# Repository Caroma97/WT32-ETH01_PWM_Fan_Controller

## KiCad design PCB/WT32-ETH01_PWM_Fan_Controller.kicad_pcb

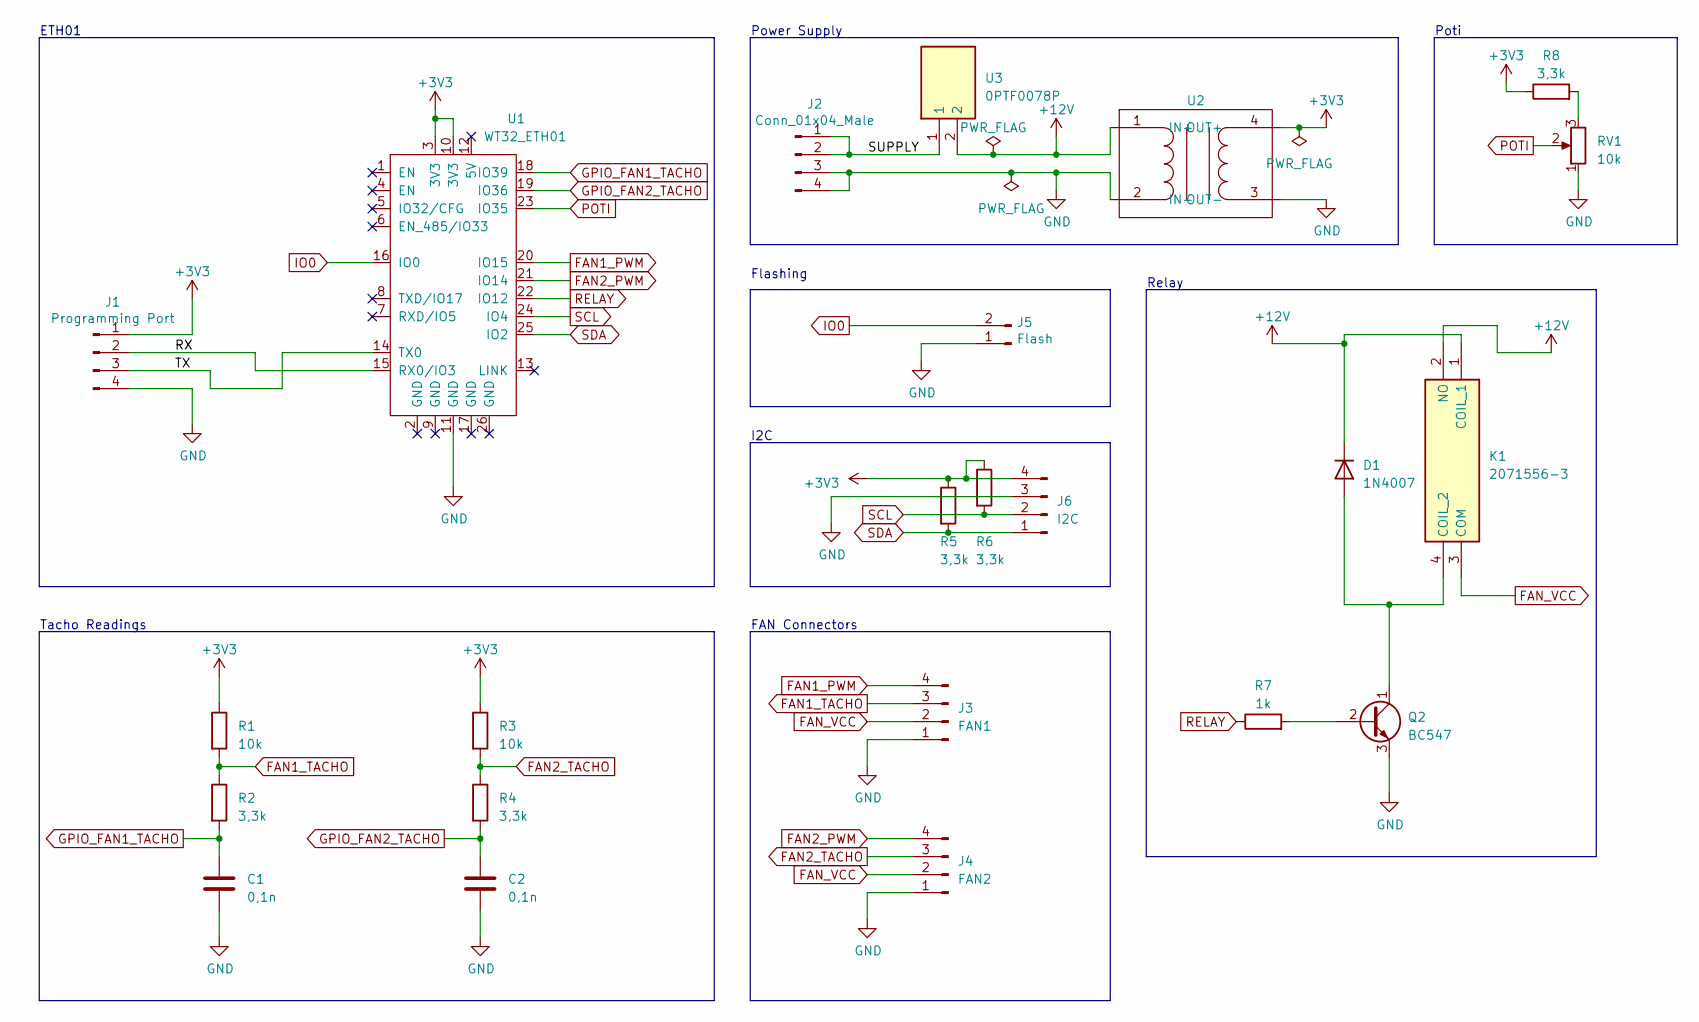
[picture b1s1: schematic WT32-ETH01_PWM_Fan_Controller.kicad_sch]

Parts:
C1, C2: 0,1n; C_Rect_L4.6mm_W2.0mm_P2.50mm_MKS02_FKP02
D1: 1N4007; D_DO-41_SOD81_P10.16mm_Horizontal
J1: Programming Port; PinHeader_1x04_P2.54mm_Vertical
J2: Conn_01x04_Male; TerminalBlock_Phoenix_MPT-0,5-4-2.54_1x04_P2.54mm_Horizontal
J3: FAN1; FanPinHeader_1x04_P2.54mm_Vertical
J4: FAN2; FanPinHeader_1x04_P2.54mm_Vertical
J5: Flash; PinHeader_1x02_P2.54mm_Vertical
J6: I2C; PinHeader_1x04_P2.54mm_Vertical
K1: 2071556-3; 20715563; Mouser Part Number 655-2071556-3
Q2: BC547; TO-92_Inline
R1, R3: 10k; R_1206_3216Metric_Pad1.30x1.75mm_HandSolder
R2, R4, R5, R6, R8: 3,3k; R_1206_3216Metric_Pad1.30x1.75mm_HandSolder
R7: 1k; R_1206_3216Metric_Pad1.30x1.75mm_HandSolder
RV1: 10k; PinHeader_1x03_P2.54mm_Vertical
U1: WT32_ETH01
U2: 2596S-ADJ_3A_DC-DC_Step_Down_Buck_Power_Module
U3: 0PTF0078P; Mouser Part Number 576-0PTF0078P

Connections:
+3V3: J1.1, J6.4, R1.1, R3.1, R5.1, R6.1, R8.1, U1.3 (3V3), U1.10 (3V3), U2.4 (OUT+)
+12V: D1.1 (K), K1.1 (COIL_1), K1.2 (NO), U2.1 (IN+), U3.2
/RX: J1.2, U1.15 (RX0/IO3)
/SUPPLY: J2.1, J2.2, U3.1
/TX: J1.3, U1.14 (TX0)
FAN1_PWM: J3.4, U1.20 (IO15)
FAN1_TACHO: J3.3, R1.2, R2.1
FAN2_PWM: J4.4, U1.21 (IO14)
FAN2_TACHO: J4.3, R3.2, R4.1
FAN_VCC: J3.2, J4.2, K1.3 (COM)
GND: C1.2, C2.2, J1.4, J2.3, J2.4, J3.1, J4.1, J5.1, J6.3, Q2.3 (E), RV1.1, U1.11 (GND), U2.2 (IN-), U2.3 (OUT-)
GPIO_FAN1_TACHO: C1.1, R2.2, U1.18 (IO39)
GPIO_FAN2_TACHO: C2.1, R4.2, U1.19 (IO36)
IO0: J5.2, U1.16 (IO0)
unnamed: D1.2 (A), K1.4 (COIL_2), Q2.1 (C)
unnamed: Q2.2 (B), R7.2
unnamed: R8.2, RV1.3
POTI: RV1.2, U1.23 (IO35)
RELAY: R7.1, U1.22 (IO12)
SCL: J6.2, R6.2, U1.24 (IO4)
SDA: J6.1, R5.2, U1.25 (IO2)

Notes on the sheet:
I2C
Power Supply
ETH01
Tacho Readings
Flashing
FAN Connectors
Poti
Relay

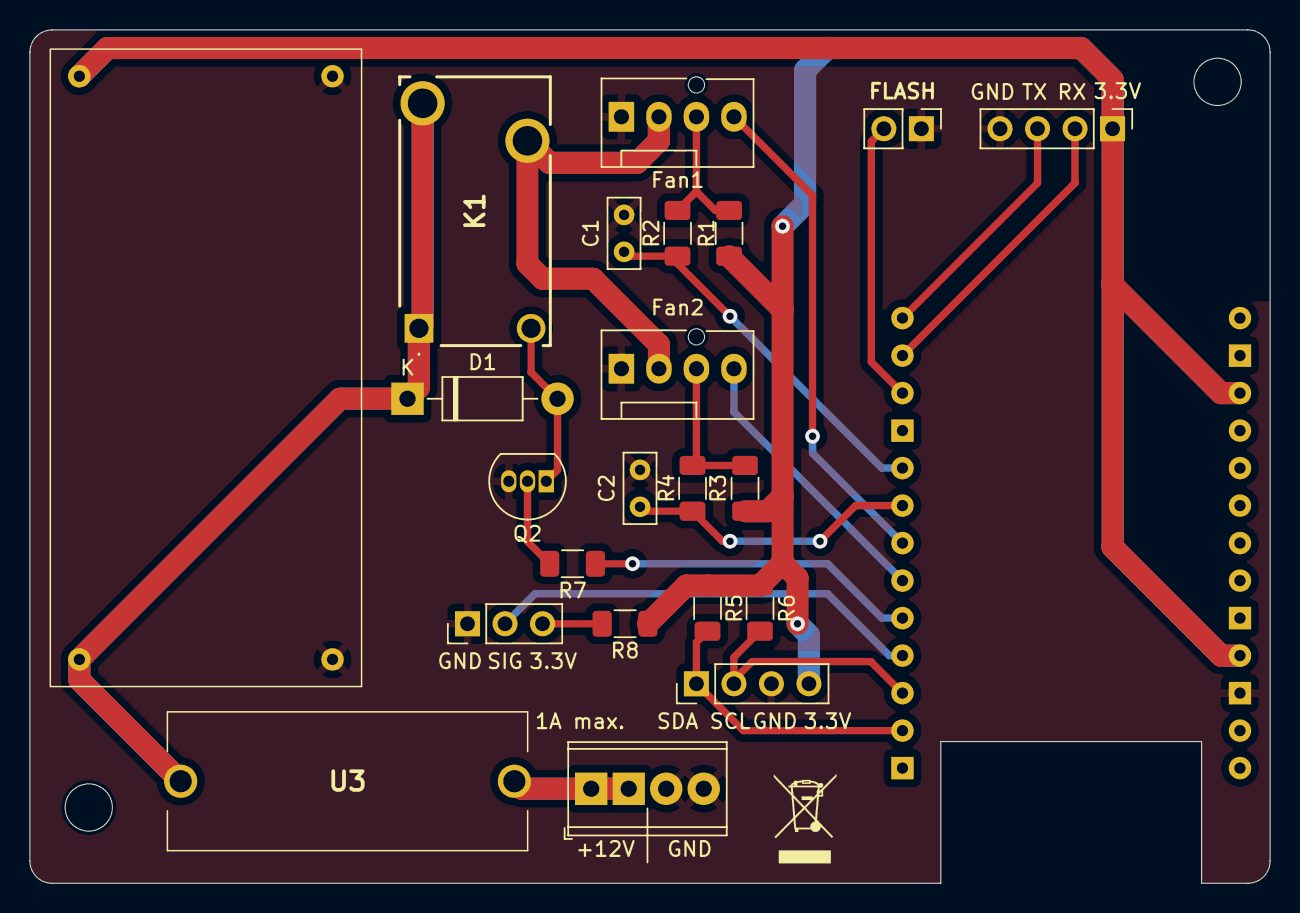
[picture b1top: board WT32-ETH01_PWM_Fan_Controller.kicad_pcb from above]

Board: 2 copper layers, 84.0 x 57.8 mm, 25 parts (1 on the bottom side), 21 nets.

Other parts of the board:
H1, H3: MountingHole; MountingHole_3.2mm_M3

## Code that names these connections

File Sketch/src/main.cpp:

/*
  Analoge Signale haben noch den Bereich vom Arduino Nano

*/

#include <Arduino.h>
#include <Seeed_BME280.h>
#include <Wire.h>

const byte PIN_fan1_pwm   =                  15; //  D5;
const byte PIN_fan1_tacho =                  39; //  A7;
const byte PIN_fan2_pwm   =                  14; //  D6;
const byte PIN_fan2_tacho =                  36; //  A6;
const byte PIN_Poti       =                  35; //  A0;
const byte PIN_Button     =                  32; //  D2;
const byte PIN_SDA        =                   2; //  A4;
const byte PIN_SCL        =                   4; //  A5;


#define interrupt_trigger_type            RISING // interrupt  triggered on a RISING input
volatile  bool interrupt_process_status = false;  // start with no switch press pending,  ie false
bool initialisation_complete            = false;  // inhibit any interrupts until initialisation is complete
const byte debounce                     =    10;  // time to wait in milli secs
byte mode                               =     0;
const byte maxMode                      =     1;

BME280 bme280;

class FAN_CONTROLLER {
  public:
    FAN_CONTROLLER(byte pin_pwm, byte pin_tacho);
    void setSpeed(int newSpeed);
    int rpm();
    int speed = 0;
    //void toggleMode();
    //byte mode = 0;

  private:
    byte _pin_pwm;
    byte _pin_tacho;
    int _speed_calculated;
    byte _maxMode = 0;
};

FAN_CONTROLLER::FAN_CONTROLLER(byte pin_pwm, byte pin_tacho) {
  pinMode(pin_pwm, OUTPUT);
  pinMode(pin_tacho, INPUT);
  analogWrite(_pin_pwm, 0);
  _pin_pwm = pin_pwm;
  _pin_tacho = pin_tacho;
}

void FAN_CONTROLLER::setSpeed(int newSpeed) {
  if (speed != newSpeed) {
    if (newSpeed <= 0) newSpeed = 0;
    else if (newSpeed >= 100) newSpeed = 100;
    else if (newSpeed == speed + 1 || newSpeed == speed - 1 ) return;
    speed = newSpeed;
    _speed_calculated= map(newSpeed, 0, 100, 0, 255);

    Serial.print(F("Setze Lüfter auf "));
    Serial.print(speed);
    Serial.print(F("% / "));
    Serial.println(_speed_calculated);

    analogWrite(_pin_pwm, _speed_calculated);
  }
}

int FAN_CONTROLLER::rpm() {
  delay(100);
  return round(0.5* analogRead(_pin_tacho));    // x0,5 da ein normaler PC Lüfter 2 Impulse pro Umdrehung ausgibt
}
/*
void FAN_CONTROLLER::toggleMode() {
  mode++;
  if (mode > _maxMode) mode = 0;
  return;    // x0,5 da ein normaler PC Lüfter 2 Impulse pro Umdrehung ausgibt
}
*/
FAN_CONTROLLER fan1(PIN_fan1_pwm, PIN_fan1_tacho);


int Mode_Auto() {
  //Serial.println(F("Reached Mode_Auto()"));
  int value = map(bme280.getTemperature(), 25, 80, 0, 100);
  if (value <= 0) return 0;
  return value;
}


int Mode_Manu() {
  //Serial.println(F("Reached Mode_Manu()"));
  int value = analogRead(PIN_Poti);
  //Serial.print(F("Analog Value: "));
  //Serial.println(value);
  return map(value, 0, 1023, 0, 100);
}




void setup() {
  delay(200);
  Serial.begin(9600);
  Serial.println(F("Starting Fan PWM Controller V0.1"));
  pinMode(PIN_Poti, INPUT);
  initialisation_complete = true; // open interrupt processing for business
  if (!bme280.init()) Serial.println(F("Device error!"));
  
}


void loop() {
  int fanValue = 0;
  switch (mode) {
    case 0:
      fanValue = Mode_Manu();
      break;
    case 1:
      fanValue = Mode_Auto();
      break;
    default:
      Serial.print(F("Unknown Mode: "));
      Serial.println(mode);
  }
  fan1.setSpeed(fanValue);
}

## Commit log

2023-11-07 PCB V0.2 Dennsh Update
2023-11-07 .ino & pictures
2023-11-07 WT32-ETH01 & VS Code
2023-11-08 Create LICENSE
    Create LICENSE
2023-11-14 Update WT32-ETH01_PWM_Fan_Controller.ino
    Final Code
